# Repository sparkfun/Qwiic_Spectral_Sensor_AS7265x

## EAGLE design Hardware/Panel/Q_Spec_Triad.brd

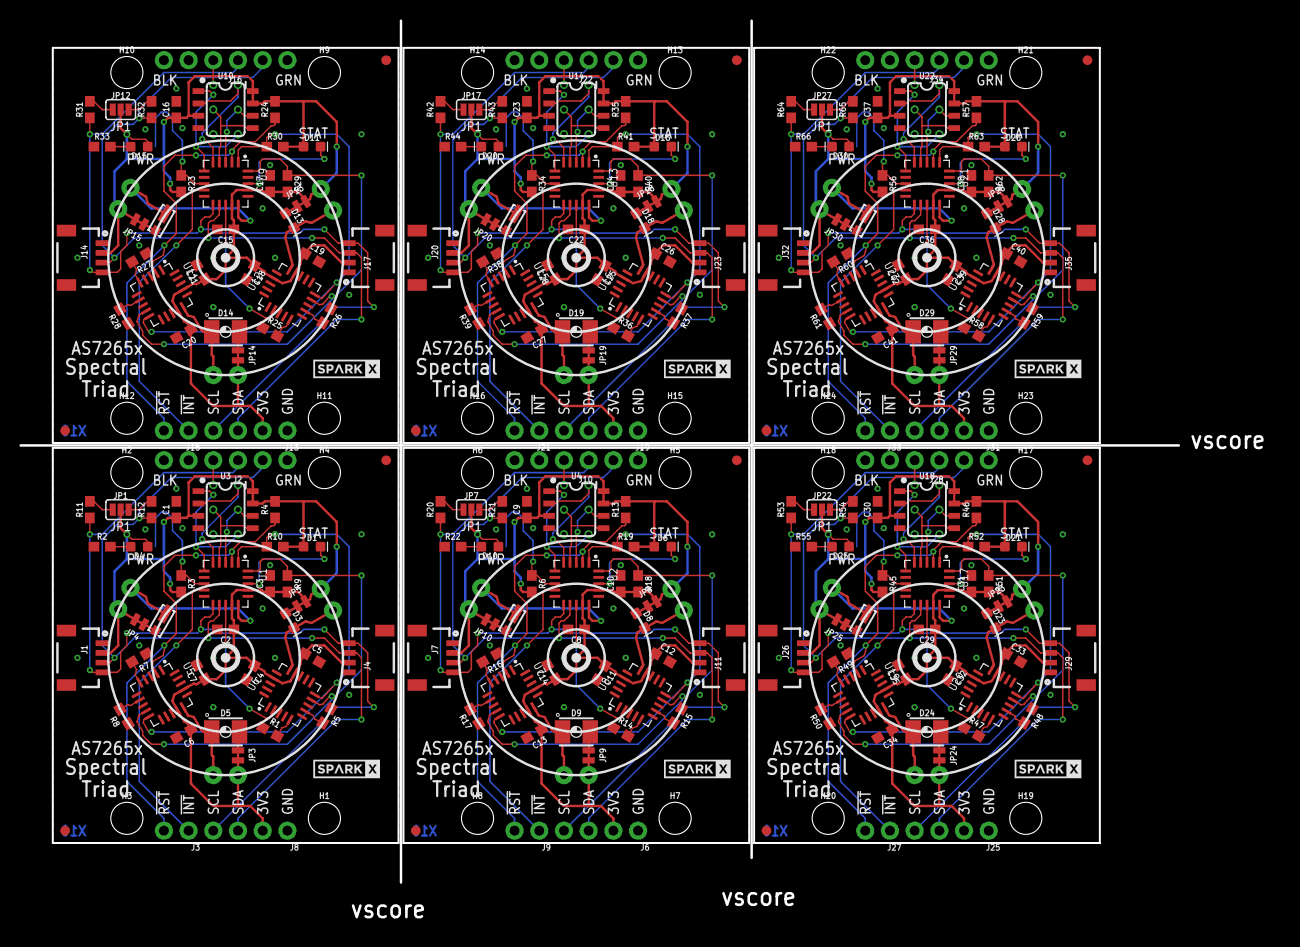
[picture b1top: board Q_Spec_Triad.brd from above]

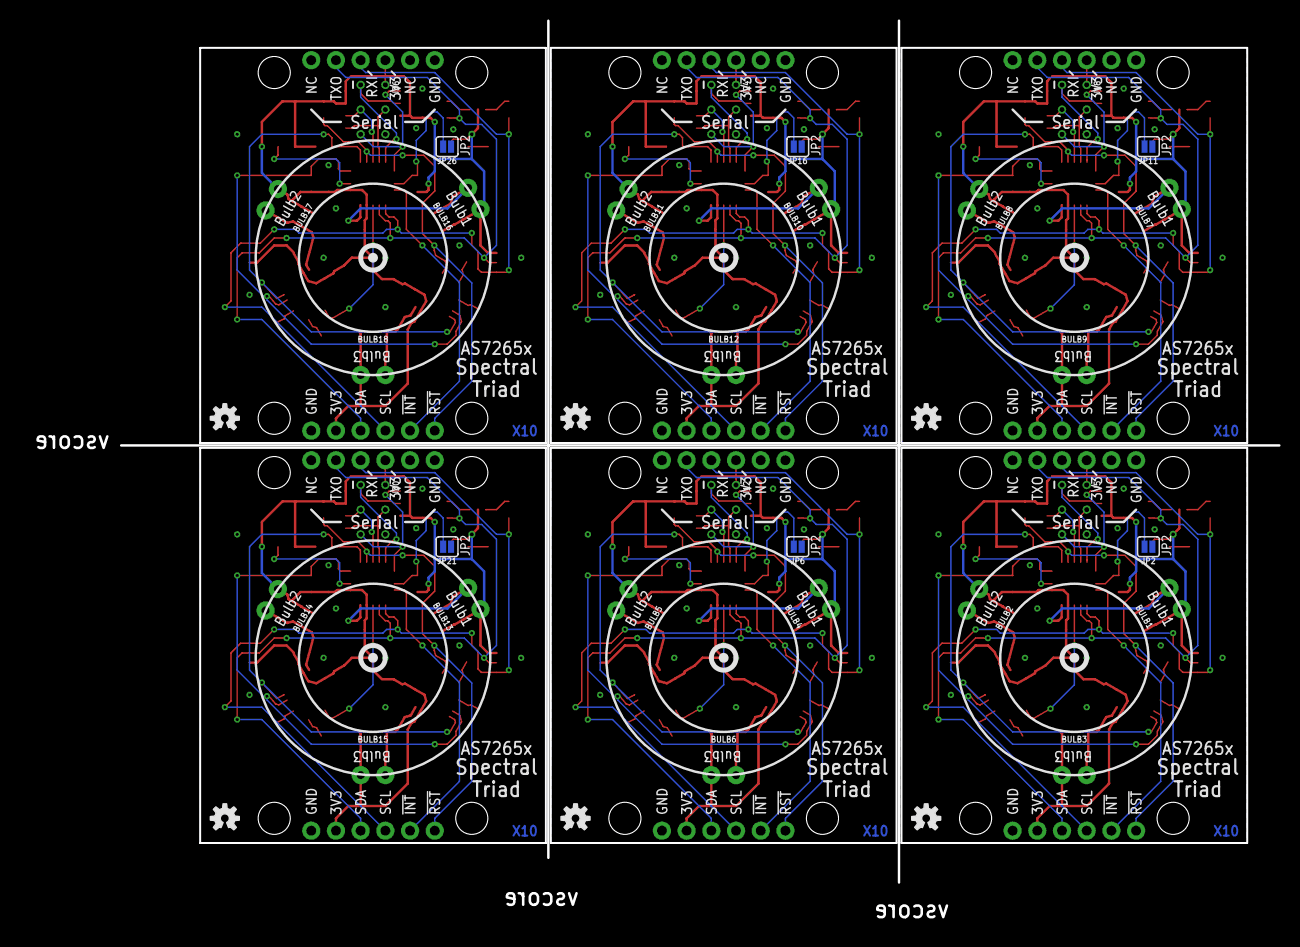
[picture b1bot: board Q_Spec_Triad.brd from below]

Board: 2 copper layers, 119.1 x 88.6 mm, 294 parts (36 on the bottom side), 168 nets.

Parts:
BULB1, BULB2, BULB3, BULB4, BULB5, BULB6, BULB7, BULB8, BULB9, BULB10, BULB11, BULB12, BULB13, BULB14, BULB15, BULB16, BULB17, BULB18: Incandescent; LED_5MM_NOSILK
C1, C9, C16, C23, C30, C37: 1.0uF; 0603
C2, C4, C6, C8, C11, C13, C15, C18, C20, C22, C25, C27, C29, C32, C34, C36, C39, C41: 0.1uF; 0603
C3, C5, C7, C10, C12, C14, C17, C19, C21, C24, C26, C28, C31, C33, C35, C38, C40, C42: 10uF; 0603
D1, D6, D11, D16, D21, D26: BLUE; LED-0603
D2, D7, D12, D17, D22, D27: 5700k; SUPER_BRIGHT_SMD_LED_1206
D3, D8, D13, D18, D23, D28: IR; LED-0603
D4, D10, D15, D20, D25, D30: RED; LED-0603
D5, D9, D14, D19, D24, D29: UV; PLCC-2
FD1, FD2, FD3, FD4, FD5, FD6, FD7, FD8, FD9, FD10, FD11, FD12: FIDUCIAL1X2; FIDUCIAL-1X2
H1, H2, H3, H4, H5, H6, H7, H8, H9, H10, H11, H12, H13, H14, H15, H16, H17, H18, H19, H20, H21, H22, H23, H24: STAND-OFF
J1, J4, J7, J11, J14, J17, J20, J23, J26, J29, J32, J35: SMD; 1X04_1MM_RA
J2, J10, J16, J22, J28, J34: Serial Interface; 1X06_NO_SILK
J3, J9, J15, J21, J27, J33: 1X02_NO_SILK
J5, J12, J18, J24, J30, J36: Flash Programming; 2X3_TEST_POINTS
J6, J8, J13, J19, J25, J31: PTH; 1X04_NO_SILK
JP1, JP7, JP12, JP17, JP22, JP27: SMT-JUMPER_3_2-NC_PASTE_SILK
JP2, JP6, JP11, JP16, JP21, JP26: SMT-JUMPER_2_NO_SILK
JP3, JP4, JP5, JP8, JP9, JP10, JP13, JP14, JP15, JP18, JP19, JP20, JP23, JP24, JP25, JP28, JP29, JP30: SMT-JUMPER_2_NC_TRACE_NO-SILK
LOGO1, LOGO2, LOGO3, LOGO4, LOGO5, LOGO6: OSHW-LOGOS; OSHW-LOGO-S
R1, R3, R4, R5, R6, R7, R8, R13, R14, R15, R16, R17, R23, R24, R25, R26, R27, R28, R34, R35, R36, R37, R38, R39, R45, R46, R47, R48, R49, R50, R56, R57, R58, R59, R60, R61: 10k; 0603
R2, R22, R33, R44, R55, R66: 1k; 0603
R9, R10, R11, R12, R18, R19, R20, R21, R29, R30, R31, R32, R40, R41, R42, R43, R51, R52, R53, R54, R62, R63, R64, R65: 2.2k; 0603
U1, U2, U9, U13, U17, U21: AS72651; LGA20
U3, U4, U10, U14, U18, U22: 4MB Flash; SO08
U5, U7, U11, U15, U19, U23: AS72653; LGA20
U6, U8, U12, U16, U20, U24: AS72652; LGA20
U$1, U$2, U$3, U$4, U$5, U$6: SPARKX-LOGO3; SPARKX-SMALL

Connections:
3.3V: BULB1.A, BULB2.A, BULB3.A, C1.1, C2.1, C3.1, C4.1, C5.1, C6.1, C7.1, D1.A, D4.A, J1.2, J2.4, J4.2, J5.2, J8.2, JP1.2, JP3.2, JP4.2, JP5.2, R3.2, R4.2, R9.2, R10.2, U1.14, U1.17, U3.3, U3.7, U3.8, U5.14, U5.17, U6.14, U6.17
3.3V1: BULB4.A, BULB5.A, BULB6.A, C8.1, C9.1, C10.1, C11.1, C12.1, C13.1, C14.1, D6.A, D10.A, J6.2, J7.2, J10.4, J11.2, J12.2, JP7.2, JP8.2, JP9.2, JP10.2, R6.2, R13.2, R18.2, R19.2, U2.14, U2.17, U4.3, U4.7, U4.8, U7.14, U7.17, U8.14, U8.17
3.3V2: BULB7.A, BULB8.A, BULB9.A, C15.1, C16.1, C17.1, C18.1, C19.1, C20.1, C21.1, D11.A, D15.A, J13.2, J14.2, J16.4, J17.2, J18.2, JP12.2, JP13.2, JP14.2, JP15.2, R23.2, R24.2, R29.2, R30.2, U9.14, U9.17, U10.3, U10.7, U10.8, U11.14, U11.17, U12.14, U12.17
3.3V3: BULB10.A, BULB11.A, BULB12.A, C22.1, C23.1, C24.1, C25.1, C26.1, C27.1, C28.1, D16.A, D20.A, J19.2, J20.2, J22.4, J23.2, J24.2, JP17.2, JP18.2, JP19.2, JP20.2, R34.2, R35.2, R40.2, R41.2, U13.14, U13.17, U14.3, U14.7, U14.8, U15.14, U15.17, U16.14, U16.17
3.3V4: BULB13.A, BULB14.A, BULB15.A, C29.1, C30.1, C31.1, C32.1, C33.1, C34.1, C35.1, D21.A, D25.A, J25.2, J26.2, J28.4, J29.2, J30.2, JP22.2, JP23.2, JP24.2, JP25.2, R45.2, R46.2, R51.2, R52.2, U17.14, U17.17, U18.3, U18.7, U18.8, U19.14, U19.17, U20.14, U20.17
3.3V5: BULB16.A, BULB17.A, BULB18.A, C36.1, C37.1, C38.1, C39.1, C40.1, C41.1, C42.1, D26.A, D30.A, J31.2, J32.2, J34.4, J35.2, J36.2, JP27.2, JP28.2, JP29.2, JP30.2, R56.2, R57.2, R62.2, R63.2, U21.14, U21.17, U22.3, U22.7, U22.8, U23.14, U23.17, U24.14, U24.17
!CS_EE: J5.5, U1.6, U3.1
!CS_EE1: J12.5, U2.6, U4.1
!CS_EE2: J18.5, U9.6, U10.1
!CS_EE3: J24.5, U13.6, U14.1
!CS_EE4: J30.5, U17.6, U18.1
!CS_EE5: J36.5, U21.6, U22.1
!INT: J3.1, U1.9
!INT1: J9.1, U2.9
!INT2: J15.1, U9.9
!INT3: J21.1, U13.9
!INT4: J27.1, U17.9
!INT5: J33.1, U21.9
!RST: J3.2, R4.1, U1.2, U5.2
!RST1: J9.2, R13.1, U2.2, U7.2
!RST2: J15.2, R24.1, U9.2, U11.2
!RST3: J21.2, R35.1, U13.2, U15.2
!RST4: J27.2, R46.1, U17.2, U19.2
!RST5: J33.2, R57.1, U21.2, U23.2
!RST-ADDR: U1.13, U6.2
!RST-ADDR1: U2.13, U8.2
!RST-ADDR2: U9.13, U12.2
!RST-ADDR3: U13.13, U16.2
!RST-ADDR4: U17.13, U20.2
!RST-ADDR5: U21.13, U24.2
GND: C1.2, C2.2, C3.2, C4.2, C5.2, C6.2, C7.2, J1.1, J2.6, J4.1, J5.6, J8.1, JP2.1, R1.1, R2.1, R5.1, R7.1, R8.1, U1.16, U3.4, U5.16, U6.16
GND1: C8.2, C9.2, C10.2, C11.2, C12.2, C13.2, C14.2, J6.1, J7.1, J10.6, J11.1, J12.6, JP6.1, R14.1, R15.1, R16.1, R17.1, R22.1, U2.16, U4.4, U7.16, U8.16
GND2: C15.2, C16.2, C17.2, C18.2, C19.2, C20.2, C21.2, J13.1, J14.1, J16.6, J17.1, J18.6, JP11.1, R25.1, R26.1, R27.1, R28.1, R33.1, U9.16, U10.4, U11.16, U12.16
GND3: C22.2, C23.2, C24.2, C25.2, C26.2, C27.2, C28.2, J19.1, J20.1, J22.6, J23.1, J24.6, JP16.1, R36.1, R37.1, R38.1, R39.1, R44.1, U13.16, U14.4, U15.16, U16.16
GND4: C29.2, C30.2, C31.2, C32.2, C33.2, C34.2, C35.2, J25.1, J26.1, J28.6, J29.1, J30.6, JP21.1, R47.1, R48.1, R49.1, R50.1, R55.1, U17.16, U18.4, U19.16, U20.16
GND5: C36.2, C37.2, C38.2, C39.2, C40.2, C41.2, C42.2, J31.1, J32.1, J34.6, J35.1, J36.6, JP26.1, R58.1, R59.1, R60.1, R61.1, R66.1, U21.16, U22.4, U23.16, U24.16
I2C_ENB: JP2.2, R3.1, U1.8
I2C_ENB1: JP6.2, R6.1, U2.8
I2C_ENB2: JP11.2, R23.1, U9.8
I2C_ENB3: JP16.2, R34.1, U13.8
I2C_ENB4: JP21.2, R45.1, U17.8
I2C_ENB5: JP26.2, R56.1, U21.8
LED_DRV: BULB1.K, D2.C, U1.15
LED_DRV1: BULB2.K, D3.C, U6.15
LED_DRV2: BULB3.K, D5.2, U5.15
LED_DRV3: BULB4.K, D7.C, U2.15
LED_DRV4: BULB5.K, D8.C, U8.15
LED_DRV5: BULB6.K, D9.2, U7.15
LED_DRV6: BULB7.K, D12.C, U9.15
LED_DRV7: BULB8.K, D13.C, U12.15
LED_DRV8: BULB9.K, D14.2, U11.15
LED_DRV9: BULB10.K, D17.C, U13.15
LED_DRV10: BULB11.K, D18.C, U16.15
LED_DRV11: BULB12.K, D19.2, U15.15
LED_DRV12: BULB13.K, D22.C, U17.15
LED_DRV13: BULB14.K, D23.C, U20.15
LED_DRV14: BULB15.K, D24.2, U19.15
LED_DRV15: BULB16.K, D27.C, U21.15
LED_DRV16: BULB17.K, D28.C, U24.15
LED_DRV17: BULB18.K, D29.2, U23.15
MISO: J5.1, U1.5, U3.2
MISO1: J12.1, U2.5, U4.2
MISO2: J18.1, U9.5, U10.2
MISO3: J24.1, U13.5, U14.2
MISO4: J30.1, U17.5, U18.2
MISO5: J36.1, U21.5, U22.2
MOSI: J5.4, U1.4, U3.5
MOSI1: J12.4, U2.4, U4.5
MOSI2: J18.4, U9.4, U10.5
MOSI3: J24.4, U13.4, U14.5
MOSI4: J30.4, U17.4, U18.5
MOSI5: J36.4, U21.4, U22.5
unnamed: D4.C, R2.2
unnamed: D1.C, U1.18
unnamed: R5.2, U6.7
unnamed: JP1.3, R12.2
unnamed: JP1.1, R11.2
unnamed: D2.A, JP4.1
unnamed: JP7.3, R21.2
unnamed: D3.A, JP5.1
unnamed: R1.2, U6.5
unnamed: JP7.1, R20.2
unnamed: D5.1, JP3.1
unnamed: R8.2, U5.7
unnamed: R7.2, U5.5
unnamed: D6.C, U2.18
unnamed: D7.A, JP10.1
unnamed: D8.A, JP8.1
unnamed: R15.2, U8.7
unnamed: R14.2, U8.5
unnamed: D9.1, JP9.1
unnamed: R17.2, U7.7
unnamed: R16.2, U7.5
unnamed: D10.C, R22.2
unnamed: JP12.3, R32.2
unnamed: JP12.1, R31.2
unnamed: D11.C, U9.18
unnamed: D12.A, JP15.1
unnamed: D13.A, JP13.1
unnamed: R26.2, U12.7
unnamed: R25.2, U12.5
unnamed: D14.1, JP14.1
unnamed: R28.2, U11.7
unnamed: R27.2, U11.5
unnamed: D15.C, R33.2
unnamed: JP17.3, R43.2
unnamed: JP17.1, R42.2
unnamed: D16.C, U13.18
unnamed: D17.A, JP20.1
unnamed: D18.A, JP18.1
unnamed: R37.2, U16.7
unnamed: R36.2, U16.5
unnamed: D19.1, JP19.1
unnamed: R39.2, U15.7
unnamed: R38.2, U15.5
unnamed: D20.C, R44.2
unnamed: JP22.3, R54.2
unnamed: JP22.1, R53.2
unnamed: D21.C, U17.18
unnamed: D22.A, JP25.1
unnamed: D23.A, JP23.1
unnamed: R48.2, U20.7
unnamed: R47.2, U20.5
unnamed: D24.1, JP24.1
unnamed: R50.2, U19.7
unnamed: R49.2, U19.5
unnamed: D25.C, R55.2
unnamed: JP27.3, R65.2
unnamed: JP27.1, R64.2
unnamed: D26.C, U21.18
unnamed: D27.A, JP30.1
unnamed: D28.A, JP28.1
unnamed: R59.2, U24.7
unnamed: R58.2, U24.5
unnamed: D29.1, JP29.1
unnamed: R61.2, U23.7
unnamed: R60.2, U23.5
unnamed: D30.C, R66.2
RX/SCL: J1.4, J2.3, J4.4, J8.4, R11.1, U1.11
RX/SCL1: J6.4, J7.4, J10.3, J11.4, R20.1, U2.11
RX/SCL2: J13.4, J14.4, J16.3, J17.4, R31.1, U9.11
RX/SCL3: J19.4, J20.4, J22.3, J23.4, R42.1, U13.11
RX/SCL4: J25.4, J26.4, J28.3, J29.4, R53.1, U17.11
RX/SCL5: J31.4, J32.4, J34.3, J35.4, R64.1, U21.11
SCK: J5.3, U1.3, U3.6
SCK1: J12.3, U2.3, U4.6
SCK2: J18.3, U9.3, U10.6
SCK3: J24.3, U13.3, U14.6
SCK4: J30.3, U17.3, U18.6
SCK5: J36.3, U21.3, U22.6
SCL_S: R9.1, U1.20, U5.9, U6.9
SCL_S1: R18.1, U2.20, U7.9, U8.9
SCL_S2: R29.1, U9.20, U11.9, U12.9
SCL_S3: R40.1, U13.20, U15.9, U16.9
SCL_S4: R51.1, U17.20, U19.9, U20.9
SCL_S5: R62.1, U21.20, U23.9, U24.9
SDA_S: R10.1, U1.1, U5.10, U6.10
SDA_S1: R19.1, U2.1, U7.10, U8.10
SDA_S2: R30.1, U9.1, U11.10, U12.10
SDA_S3: R41.1, U13.1, U15.10, U16.10
SDA_S4: R52.1, U17.1, U19.10, U20.10
SDA_S5: R63.1, U21.1, U23.10, U24.10
TX/SDA: J1.3, J2.2, J4.3, J8.3, R12.1, U1.12
TX/SDA1: J6.3, J7.3, J10.2, J11.3, R21.1, U2.12
TX/SDA2: J13.3, J14.3, J16.2, J17.3, R32.1, U9.12
TX/SDA3: J19.3, J20.3, J22.2, J23.3, R43.1, U13.12
TX/SDA4: J25.3, J26.3, J28.2, J29.3, R54.1, U17.12
TX/SDA5: J31.3, J32.3, J34.2, J35.3, R65.1, U21.12

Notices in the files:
parts and their libraries:
SparkFun-Aesthetics: Licensing: Creative Commons ShareAlike 4.0 International - https://creativecommons.org/licenses/by-sa/4.0
